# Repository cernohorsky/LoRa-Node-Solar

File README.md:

# LoRa Node

It uses the MCP73871 - USB/Solar panel charger and very nice TPS63031 Buck-Boost Converter. Main benefits of the board is small size and possibility to run literally forever from one small single cell LiPo battery.

It's necessary to <b>burn bootloader with ISP before RFM95W module is soldered</b>.

<b>ToDo:</b><br>
Change ground symbols<br>
Create BOM<br>

#RFM95W, #ATMEGA328P,  #TPS63031, #MCP7381, #Arduino

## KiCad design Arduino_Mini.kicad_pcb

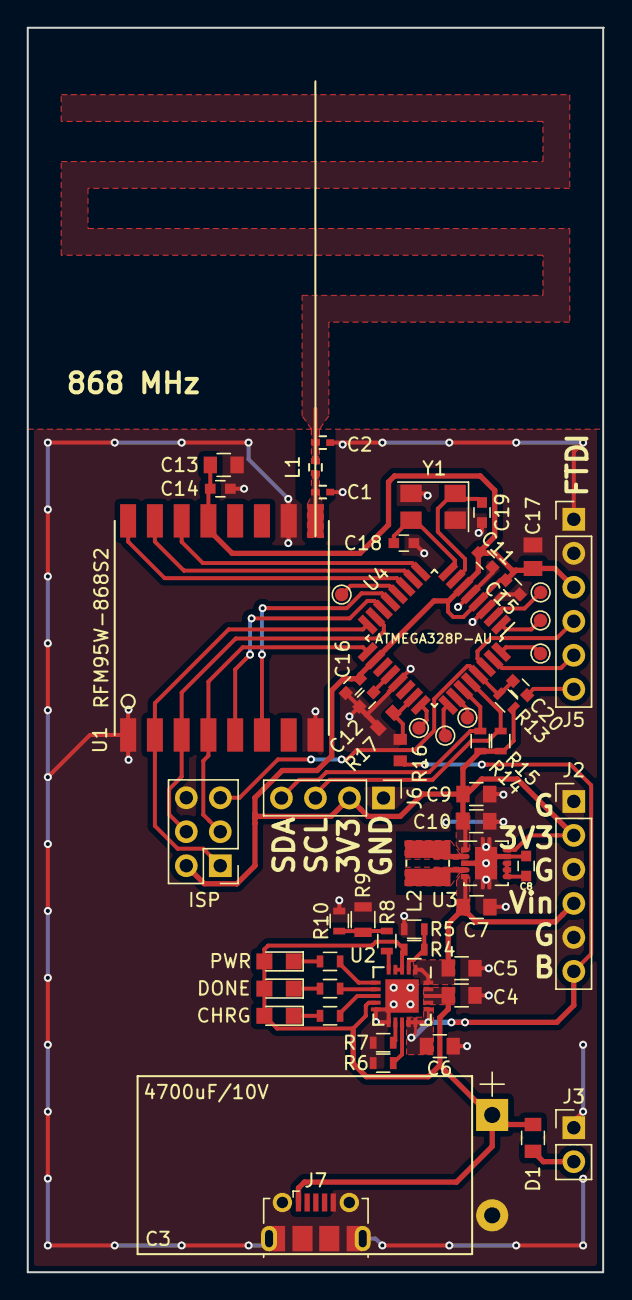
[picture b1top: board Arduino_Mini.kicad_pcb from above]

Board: 2 copper layers, 43.0 x 93.0 mm, 59 parts (0 on the bottom side), 47 nets.

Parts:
C1, C2: C; C_0402
C3: 4700uF/10V; CP_Radial_D12.5mm_P25mm
C4, C5, C6, C7, C9, C10, C13: 10u; C_0805
C8, C11, C12, C14, C15, C16, C20: 100n; C_0603
C17: 10u; C_0805_2012Metric
C18, C19: 15p; C_0603
D1: MBR120VLSFT1G; C_0805
D2: CHRG; LED_0805
D3: DONE; LED_0805
D4: PWR; LED_0805
J2, J5: Conn_01x06; Pin_Header_Straight_1x06_Pitch2.54mm
J3: Conn_01x02; Pin_Header_Straight_1x02_Pitch2.54mm
J4: ISP; Pin_Header_Straight_2x03_Pitch2.54mm
J6: Conn_01x04; Pin_Header_Straight_1x04_Pitch2.54mm
J7: USB_B_Micro; USB_Micro-B_Molex-105017-0001
J8: D2; TestPoint_Pad_D1.0mm
J9: D3; TestPoint_Pad_D1.0mm
J10: D4; TestPoint_Pad_D1.0mm
J11: A1; TestPoint_Pad_D1.0mm
J12: A2; TestPoint_Pad_D1.0mm
J13: A3; TestPoint_Pad_D1.0mm
J14: D8; TestPoint_Pad_D1.0mm
L1: L; C_0402
L2: 1u5; Inductor_Wurth_MAPI-3012
R1, R2, R3, R8: 1k; R_0603
R4: 270k; R_0603
R5, R7: 100k; R_0603
R6: 2k; R_0603
R9: THERM 10k; R_0805
R10: 150k; R_0603
R13, R14, R15: 4k7; R_0603
R16: 220k; R_0603_1608Metric
R17: 100k; R_0603_1608Metric
U1: RFM95W-868S2; RFM95W
U2: MCP73871; QFN-20-1EP_4x4mm_Pitch0.5mm
U3: TPS63031; Texas_S-PVSON-N10
U4: ATMEGA328P-AU; TQFP-32_7x7mm_Pitch0.8mm
Y1: Crystal_GND24_Small; Crystal_SMD_5032-4pin_5.0x3.2mm

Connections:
+3V3: C9.1, C10.2, C11.1, C13.1, C14.1, C15.1, C16.1, C17.1, J2.2, J4.2, J5.3, J6.2, R13.1, R14.1, R15.1, U1.13, U3.1, U3.10, U4.4, U4.6, U4.18
/10(**/SS): U1.5, U4.14
/11(MISO): J4.4, U1.3, U4.15
/12(**/MOSI): J4.1, U1.2, U4.16
/13(SCK): J4.3, U1.4, U4.17
/A0: R16.2, R17.1, U4.23
/A1: J11.1, U4.24
/A2: J12.1, U4.25
/A3: J13.1, U4.26
/ANT: C2.1, L1.2
/D0/RX: J5.4, U4.30
/D1/TX: J5.5, U4.31
/D2: J8.1, U4.32
/D3: J9.1, U4.1
/D4: J10.1, U4.2
/D5: U1.14, U4.9
/D6: U1.15, U4.10
/D7: U1.16, U4.11
/D8: J14.1, U4.12
/D9: U1.6, U4.13
/DTR: C20.2, J5.6
/RES: C20.1, J4.5, R13.2, U4.29
/SCL: J6.3, R15.2, U4.28
/SDA: J6.4, R14.2, U4.27
/VBAT: C6.1, J2.6, R16.1, U2.14, U2.15, U2.16
/VOUT: C5.1, C7.1, J2.4, U2.1, U2.20, U3.5
/VSOL: D1.2, J3.2
Earth: C1.2, C2.2, C3.2, C4.2, C5.2, C6.2, C7.2, C8.2, C9.2, C10.1, C11.2, C12.2, C13.2, C14.2, C15.2, C16.2, C17.2, C18.2, C19.2, J2.1, J2.3, J2.5, J3.1, J4.6, J5.1, J5.2, J6.1, J7.5, J7.6, R5.2, R6.2, R7.2, R9.1, R10.1, R17.2, U1.1, U1.8, U1.10, U2.10, U2.11, U2.21, U3.3, U3.9, U3.11, U4.3, U4.5, U4.21, Y1.2, Y1.4
unnamed: C1.1, L1.1, U1.9
unnamed: C8.1, U3.6, U3.7, U3.8
unnamed: C12.1, U4.20
unnamed: C18.1, U4.8, Y1.3
unnamed: C19.1, U4.7, Y1.1
unnamed: D2.1, R1.1
unnamed: D3.1, R2.1
unnamed: D4.1, R3.1
unnamed: L2.1, U3.4
unnamed: L2.2, U3.2
unnamed: R1.2, U2.8
unnamed: R2.2, U2.7
unnamed: R3.2, U2.6
unnamed: R4.2, R5.1, U2.2
unnamed: R6.1, U2.13
unnamed: R7.1, U2.12
unnamed: R8.2, U2.5
unnamed: R8.1, R9.2, R10.2
VCC: C3.1, C4.1, D1.1, D2.2, D3.2, D4.2, J7.1, R4.1, U2.3, U2.4, U2.9, U2.17, U2.18, U2.19

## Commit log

2019-03-13 SPI bugfix, FTDI reset bugfix, GPIO pads addition
2019-03-13 Changed Antenna dimension, changed TPS63031 footprint
2019-03-22 Added lib files
2019-03-22 Added antenna measurement result, added actual pcb image
